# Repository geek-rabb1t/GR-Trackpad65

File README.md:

# GR-Trackpad65

Trackpad module designed for a keyboard named Futaba.

Azoteq's TPS65 trackpad module has been discontinued, so I designed a trackpad to achieve the same size.

The controller IC is the IQS550, which is also used in the TPS65.  
Therefore, modules designed to use the TPS65 may be used without modification.

There is no compatibility in the settings to be written to the IQS550, just the same module size and pin assignments.

## Overview

### Appearance

| Top side | Bottom side |
|---|---|
|||

### Dimensions

|  | Length | Width |
|---| --- | ---|
| Trackpad only |49mm | 65mm |
| with sacrificed plate |49mm |79mm |

### Pin assign

Pin assignments for FFC connectors.
From left to right.

| No. |  |
|---| --- |
| 1 | RDY |
| 2 | NRST |
| 3 | GND |
| 4 | VCC |
| 5 | SCL |
| 6 | SDA |

## PCB Specifications

No special settings are required, but if manufactured on a PCB other than 1.6 mm thick, it may not work well.

| 項目 | Value | note |
| --- | --- | --- |
| Layers | 4 |  |
| PCB Thickness | 1.6mm |  |
| Tooling holes | Added by Customer | Option for PCBA. (Only JLCPCB) |

### Bill of Materials

The parts required for manufacturing are listed below.

| Part Detail | Reference | Quantity | Note |
| --- | --- | --- | --- |
| Azoteq IQS550BLQNR | U1 | 1 | Controller IC |
| JUSHUO AFC07-S06FCC-00  | J1 | 1 | FFC connector |
| Capacitor(100nF) | C1,C6 | 2 | 0603 Package |
| Capacitor(100pF) | C2,C4 | 2 | 0603 Package |
| Capacitor(1uF) | C3,C5 | 2 | 0603 Package |
| Resistor(4.7kΩ) | R1,R2 | 2 | 0603 Package |
| Resistor(1kΩ) | R3 - R12 | 10 | 0603 Package |

## Surface material of trackpad

Be sure to attach some kind of material to the surface of the trackpad.  
If you use the trackpad without attaching any material, it will not work properly.

The recommended material is 2mm thick matte acrylic. 
If other materials are used, adjust the setting value according to the environment.

## Writing configuration

**It does not function as a trackpad when just manufactured.
It is necessary to write the configuration to the controller IC.**

The trackpad configuration is located in `config` directory.

| File name | Description |
| --- | --- |
| gr-trackpad65.ini | Trackpad configuration file to be set temporarily from the debug tool. |
| gr-trackpad65_Vx.x.hex  | Pre-configured firmware. Normally use this one. |

To write the configuration, you will need Azoteq's CT210A writing tool.

- https://mou.sr/3Z9SMgG

Special software is required to write configuration and debug the trackpad.
These can be downloaded from Azoteq's website.

https://www.azoteq.com/design/software-and-tools/

- IQS5XX B000 GUI  
Use this to debug the trackpad and write configuration.
- IQS5XX Flash Programmer  
This can also be used if you only want to write preconfigured binaries.

The usage of the tool and specifications of the controller IC are documented on Azoteq's website.
Please refer to these documents for setting up.

- [IQS550/572/525-B000 DATASHEET](https://www.azoteq.com/images/stories/pdf/iqs5xx-b000_trackpad_datasheet.pdf)
- [AZD087 - Setup and user guide for the IQS5XX-B000 series](https://www.azoteq.com/images/stories/pdf/AZD087%20-%20IQS5xx-B000%20Setup%20and%20User%20Guide.pdf)

Various other documents can be accessed from this page and referred to as necessary.

https://www.azoteq.com/design/application-notes/

---

# GR-Trackpad65

Futabaというキーボード用に設計したトラックパッドモジュールです。

Azoteq社の TPS65 というトラックパッドモジュールが製造中止になってしまったので、  
同じサイズのトラックパッドを実現するために設計しました。

コントローラーICには、TPS65 でも使用している IQS550 を採用しています。  
そのため、TPS65 を使用するように設計されたモジュールでもそのまま使用できる可能性があります。

モジュールサイズやピンアサインが同じだけで、IQS550に書き込む設定に互換性はありません。

## モジュール概要

### 外観

| 表 | 裏 |
|---|---|
|||

### サイズ

|  | 縦 | 横 |
|---| --- | ---|
| トラックパッド本体 |49mm | 65mm |
| PCBA用の捨て板付き |49mm |79mm |

### ピンアサイン

FFCコネクタのピンアサイン。  
左から順に。

| No. |  |
|---| --- |
| 1 | RDY |
| 2 | NRST |
| 3 | GND |
| 4 | VCC |
| 5 | SCL |
| 6 | SDA |

## 製造データ

特に特別な設定は必要ありませんが、1.6mm厚以外のPCBで製造した場合、上手く動かない可能性があります。

| 項目 | 値 | メモ |
| --- | --- | --- |
| 層数 | 4層PCB |  |
| PCB の厚さ | 1.6mm厚 |  |
| Tooling holes | Added by Customer | PCBAの設定項目 (JLCPCBに発注する場合) |

### 必要なパーツリスト

発注時に以下のパーツを指定して、PCBAを依頼してください。  
JLCPCBに発注する場合は、ガーバーファイルに必要な情報が含まれています。  
他のベンダーに依頼する場合や、パーツが不明な場合は以下のパーツを指定してください。  

| パーツ | 使用箇所 | 必要数(1枚当たり) | メモ |
| --- | --- | --- | --- |
| Azoteq IQS550BLQNR | U1 | 1 | コントローラーIC |
| JUSHUO AFC07-S06FCC-00  | J1 | 1 | FFCコネクタ |
| キャパシタ(100nF) | C1,C6 | 2 | 0603サイズ |
| キャパシタ(100pF) | C2,C4 | 2 | 0603サイズ |
| キャパシタ(1uF) | C3,C5 | 2 | 0603サイズ |
| 抵抗(4.7kΩ) | R1,R2 | 2 | 0603サイズ |
| 抵抗(1kΩ) | R3 - R12 | 10 | 0603サイズ |

## トラックパッドの表面素材について

トラックパッドの表面には、必ず何らかの素材を貼り付けて下さい。  
何も貼り付けずに使用すると正しく動作しません。

推奨は2mm厚のマットアクリルです。他の素材使う場合は、環境に合わせて設定値をを調整してください。

## 設定値について

**製造しただけの状態では、トラックパッドとして機能しません。
コントローラーICに設定値を書き込む必要があります。**

標準的な設定は、 `config` ディレクトリに置いてあります。

| ファイル | 用途 |
| --- | --- |
| gr-trackpad65.ini | デバッグツールから一時的に設定するトラックパッドの設定ファイル。 |
| gr-trackpad65_Vx.x.hex  | 設定済みのファームウェア。通常はこちらを使用してください。 |

設定値の書き込みには Azoteq社のCT210A という書き込みツールが必要です。
MouserやDigiKeyで7000円くらいで調達できます。

- https://mou.sr/4i2krZd
- https://www.digikey.jp/short/39892pvp

設定の書き込みやトラックパッドのデバッグには専用のソフトウェアが必要となります。
これらはAzoteq社のホームページからダウンロード可能です。

https://www.azoteq.com/design/software-and-tools/

- IQS5XX B000 GUI  
トラックパッドのデバッグや設定の書き込みにはこちらを使用します。
- IQS5XX Flash Programmer  
設定済みのバイナリの書き込みだけの場合はこちらも使用可能です。

ツールの使い方やコントローラーICの仕様はAzoteq社のホームページ上にドキュメントがあります。
これらを参考に設定してください。

- [IQS550/572/525-B000 DATASHEET](https://www.azoteq.com/images/stories/pdf/iqs5xx-b000_trackpad_datasheet.pdf)
- [AZD087 - Setup and user guide for the IQS5XX-B000 series](https://www.azoteq.com/images/stories/pdf/AZD087%20-%20IQS5xx-B000%20Setup%20and%20User%20Guide.pdf)

その他、こちらのページから様々なドキュメントにアクセスできますので必要に応じて参照してください。

https://www.azoteq.com/design/application-notes/

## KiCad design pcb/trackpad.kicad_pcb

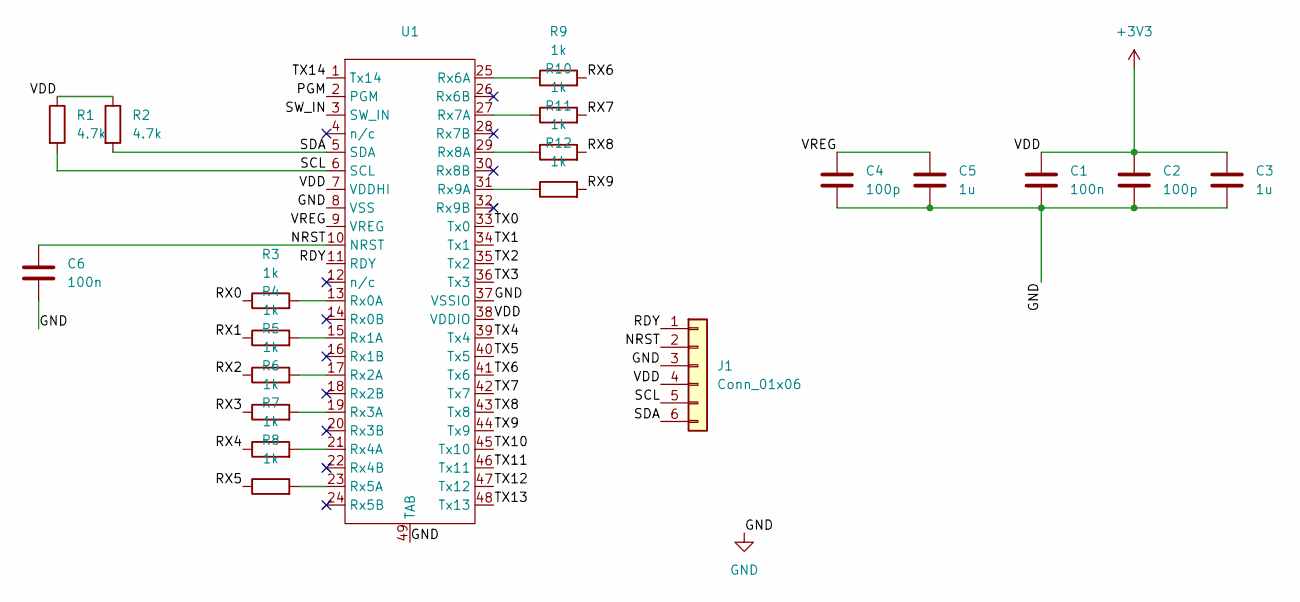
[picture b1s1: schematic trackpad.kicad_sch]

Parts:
C1, C6: 100n; C_0603_1608Metric
C2, C4: 100p; C_0603_1608Metric
C3, C5: 1u; C_0603_1608Metric
J1: Conn_01x06; Jushuo_AFC07-S06FCA-00_1x6-1MP_P0.50_Horizontal-JLC; LCSC Part # C11048
R1, R2: 4.7k; R_0603_1608Metric
R3, R4, R5, R6, R7, R8, R9, R10, R11, R12: 1k; R_0603_1608Metric
U1: QFN-48-1EP_7x7mm_P0.5mm_EP3.5x3.5mm

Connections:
+3V3: C1.1, C2.1, C3.1, J1.4, R1.1, R2.1, U1.7 (VDDHI), U1.38 (VDDIO)
/NRST: C6.1, J1.2, U1.10 (NRST)
/PGM: U1.2 (PGM)
/RDY: J1.1, U1.11 (RDY)
/RX0: R3.1
/RX1: R4.1
/RX2: R5.1
/RX3: R6.1
/RX4: R7.1
/RX5: R8.1
/RX6: R9.2
/RX7: R10.2
/RX8: R11.2
/RX9: R12.2
/SCL: J1.5, R1.2, U1.6 (SCL)
/SDA: J1.6, R2.2, U1.5 (SDA)
/SW_IN: U1.3 (SW_IN)
/TX0: U1.33 (Tx0)
/TX1: U1.34 (Tx1)
/TX2: U1.35 (Tx2)
/TX3: U1.36 (Tx3)
/TX4: U1.39 (Tx4)
/TX5: U1.40 (Tx5)
/TX6: U1.41 (Tx6)
/TX7: U1.42 (Tx7)
/TX8: U1.43 (Tx8)
/TX9: U1.44 (Tx9)
/TX10: U1.45 (Tx10)
/TX11: U1.46 (Tx11)
/TX12: U1.47 (Tx12)
/TX13: U1.48 (Tx13)
/TX14: U1.1 (Tx14)
/VREG: C4.1, C5.1, U1.9 (VREG)
GND: C1.2, C2.2, C3.2, C4.2, C5.2, C6.2, J1.3, U1.8 (VSS), U1.37 (VSSIO), U1.49 (TAB)
unnamed: R3.2, U1.13 (Rx0A)
unnamed: R4.2, U1.15 (Rx1A)
unnamed: R5.2, U1.17 (Rx2A)
unnamed: R6.2, U1.19 (Rx3A)
unnamed: R7.2, U1.21 (Rx4A)
unnamed: R8.2, U1.23 (Rx5A)
unnamed: R9.1, U1.25 (Rx6A)
unnamed: R10.1, U1.27 (Rx7A)
unnamed: R11.1, U1.29 (Rx8A)
unnamed: R12.1, U1.31 (Rx9A)

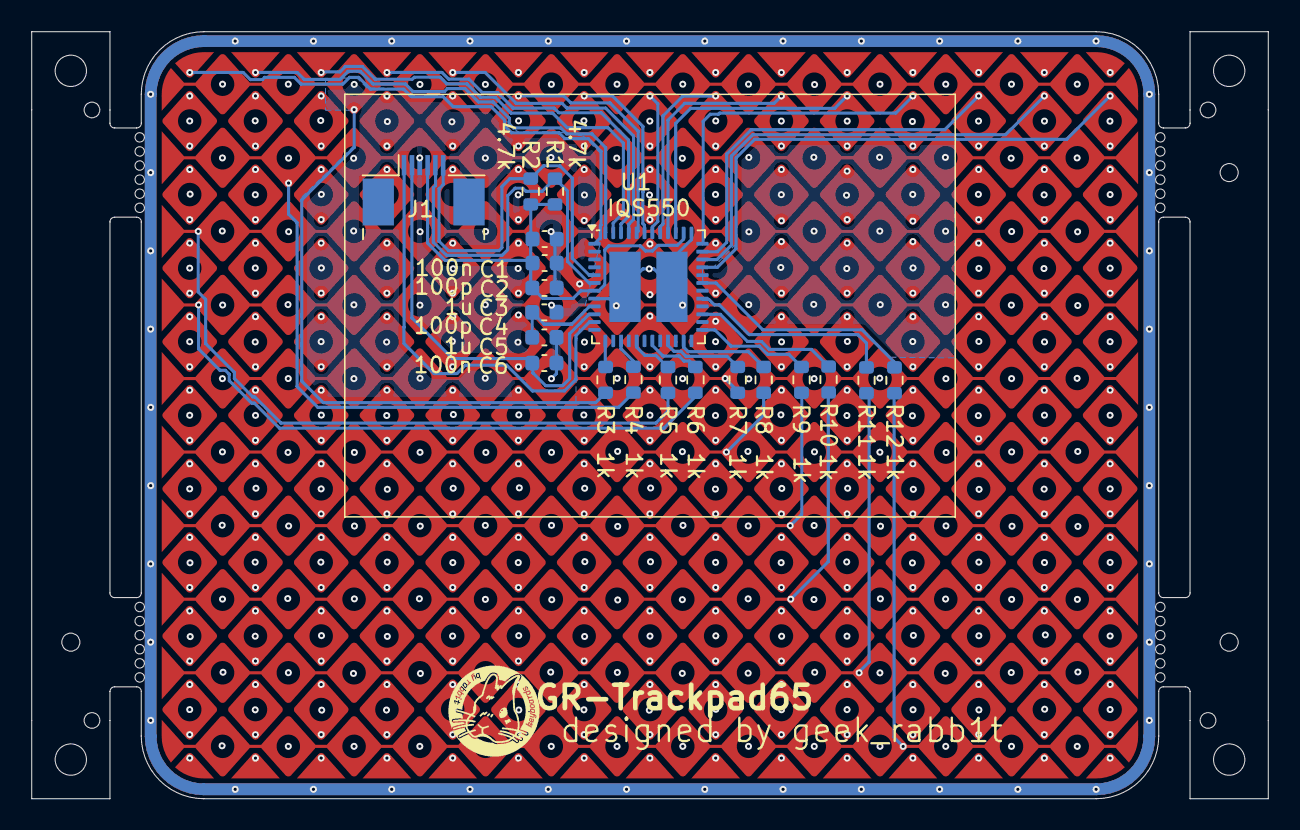
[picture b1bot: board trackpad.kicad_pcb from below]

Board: 4 copper layers, 79.0 x 49.0 mm, 20 parts (20 on the bottom side), 17 nets.

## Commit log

2024-11-13 Add pcb data
2024-11-13 Add overlay outline for laser cutting
2024-11-19 Add config data.
2024-11-23 Update readme.
2024-11-23 Rename config file.
2025-01-18 Fix silkscreen
